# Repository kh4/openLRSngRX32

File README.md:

openLRSngRX32
=============

OpenLRS compatible 12 channel RX based on STM32F103. Can use up to 2 RFM22B radio modules for true diversity and supports additional MPU6050 for integrated flightcontrol.

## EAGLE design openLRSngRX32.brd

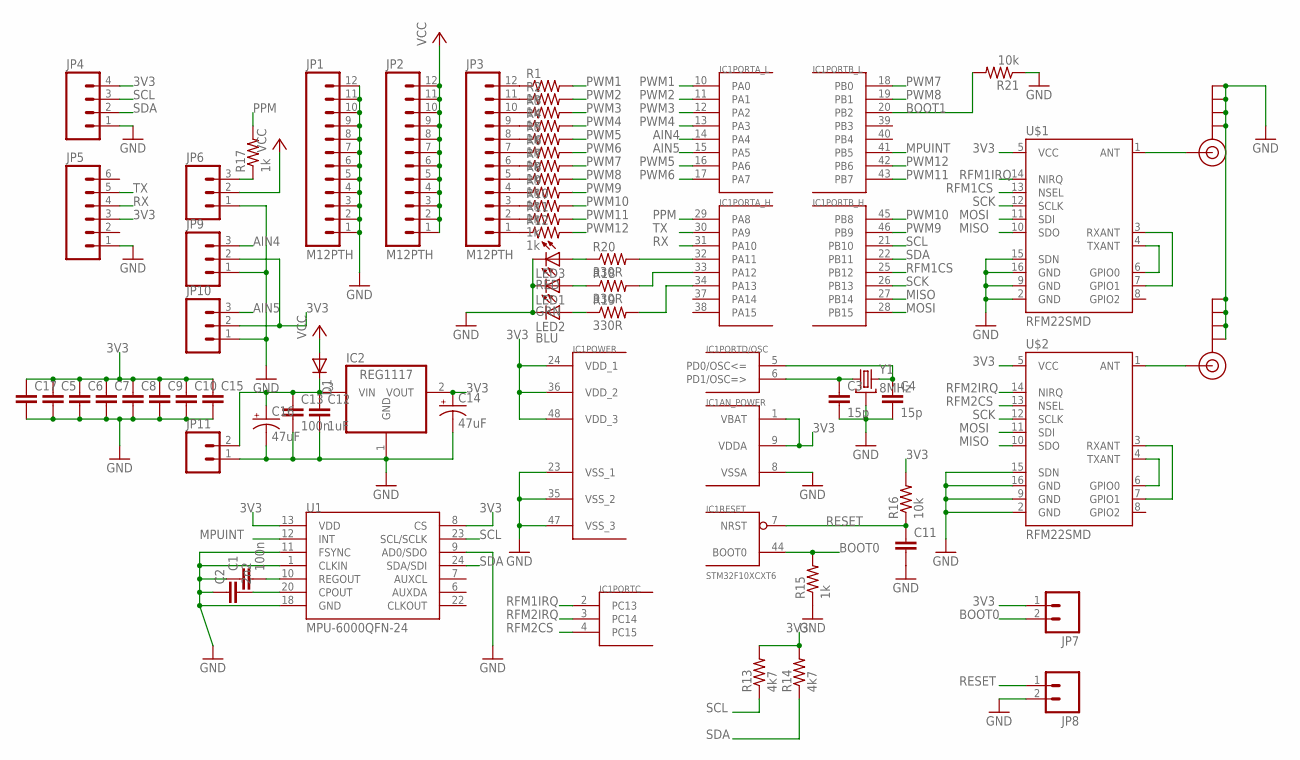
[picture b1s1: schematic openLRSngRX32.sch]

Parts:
C1, C13: 100n; 0805
C2: 2n2; 0805
C3, C4: 15p; 0805
C5, C6, C7, C8, C9, C10, C11, C15, C17: CAP0805; 0805
C12: 1uF; 0805
C14, C16: 47uF; EIA3528
D1: DIODE-DO-214AC; DO-214AC
IC1: STM32F10XCXT6; TQFP48
IC2: REG1117; SOT223
J$1, J$2: SMA_EDGE; SMA-EDGE
JP1, JP2, JP3: M12PTH; 1X12
JP4: M04PTH; 1X04
JP5: M06SIP; 1X06
JP6, JP9, JP10: M03PTH; 1X03
JP7, JP8, JP11: M02PTH; 1X02
LED1: GRN; SML0805
LED2: BLU; SML0805
LED3: RED; SML0805
R1, R2, R3, R4, R5, R6, R7, R8, R9, R10, R11, R12, R15, R17: 1k; 0805
R13, R14: 4k7; 0805
R16, R21: 10k; 0805
R18, R19, R20: 330R; 0805
U1: MPU-6000QFN-24; QFN-24-TESTING
U$1, U$2: RFM22SMD; RFM22-XXX-S2
Y1: 8MHz; CRYSTAL-SMD-5X3

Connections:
3V3: C5.1, C6.1, C7.1, C8.1, C9.1, C10.1, C14.A (+), C15.1, C17.1, IC1.1 (VBAT), IC1.9 (VDDA), IC1.24 (VDD_1), IC1.36 (VDD_2), IC1.48 (VDD_3), IC2.2 (VOUT), JP4.4, JP5.3, JP7.1, JP9.2, JP10.2, R13.2, R14.2, R16.2, U1.8 (CS), U1.13 (VDD), U$1.5 (VCC), U$2.5 (VCC)
AIN4: IC1.14 (PA4), JP9.3
AIN5: IC1.15 (PA5), JP10.3
BOOT0: IC1.44 (BOOT0), JP7.2, R15.2
BOOT1: IC1.20 (PB2), R21.2
GND: C1.1, C2.1, C3.2, C4.2, C5.2, C6.2, C7.2, C8.2, C9.2, C10.2, C11.2, C12.2, C13.2, C14.C (-), C15.2, C16.C (-), C17.2, IC1.8 (VSSA), IC1.23 (VSS_1), IC1.35 (VSS_2), IC1.47 (VSS_3), IC2.1 (GND), J$1.GND@0 (GND), J$1.GND@1 (GND), J$1.GND@2 (GND), J$1.GND@3 (GND), J$2.GND@0 (GND), J$2.GND@1 (GND), J$2.GND@2 (GND), J$2.GND@3 (GND), JP1.1, JP1.2, JP1.3, JP1.4, JP1.5, JP1.6, JP1.7, JP1.8, JP1.9, JP1.10, JP1.11, JP1.12, JP4.1, JP5.1, JP6.1, JP8.2, JP9.1, JP10.1, JP11.1, LED1.C, LED2.C, LED3.C, R15.1, R21.1, U1.1 (CLKIN), U1.9 (AD0/SDO), U1.11 (FSYNC), U1.18 (GND), U$1.2 (GND), U$1.9 (GND), U$1.15 (SDN), U$1.16 (GND), U$2.2 (GND), U$2.9 (GND), U$2.15 (SDN), U$2.16 (GND), Y1.2 (GND), Y1.4 (GND)
MISO: IC1.27 (PB14), U$1.10 (SDO), U$2.10 (SDO)
MOSI: IC1.28 (PB15), U$1.11 (SDI), U$2.11 (SDI)
MPUINT: IC1.41 (PB5), U1.12 (INT)
unnamed: JP3.12, R1.1
unnamed: JP3.11, R2.1
unnamed: JP3.10, R3.1
unnamed: JP3.9, R4.1
unnamed: JP3.8, R5.1
unnamed: JP3.7, R6.1
unnamed: JP3.6, R7.1
unnamed: JP3.5, R8.1
unnamed: JP3.4, R9.1
unnamed: JP3.3, R10.1
unnamed: JP3.2, R11.1
unnamed: JP3.1, R12.1
unnamed: J$2.SIG (SIGNAL), U$2.1 (ANT)
unnamed: C1.2, U1.10 (REGOUT)
unnamed: C2.2, U1.20 (CPOUT)
unnamed: C4.1, IC1.5 (PD0/OSC<=), Y1.3 (2)
unnamed: C3.1, IC1.6 (PD1/OSC=>), Y1.1
unnamed: J$1.SIG (SIGNAL), U$1.1 (ANT)
unnamed: U$2.4 (TXANT), U$2.6 (GPIO0)
unnamed: U$2.3 (RXANT), U$2.7 (GPIO1)
unnamed: U$1.4 (TXANT), U$1.6 (GPIO0)
unnamed: U$1.3 (RXANT), U$1.7 (GPIO1)
unnamed: JP6.3, R17.1
unnamed: C12.1, C13.1, C16.A (+), D1.C, IC2.3 (VIN), JP11.2
unnamed: LED3.A, R20.1
unnamed: LED1.A, R18.1
unnamed: LED2.A, R19.1
unnamed: IC1.32 (PA11), R20.2
unnamed: IC1.33 (PA12), R18.2
unnamed: IC1.34 (PA13), R19.2
PPM: IC1.29 (PA8), R17.2
PWM1: IC1.10 (PA0), R1.2
PWM2: IC1.11 (PA1), R2.2
PWM3: IC1.12 (PA2), R3.2
PWM4: IC1.13 (PA3), R4.2
PWM5: IC1.16 (PA6), R5.2
PWM6: IC1.17 (PA7), R6.2
PWM7: IC1.18 (PB0), R7.2
PWM8: IC1.19 (PB1), R8.2
PWM9: IC1.46 (PB9), R9.2
PWM10: IC1.45 (PB8), R10.2
PWM11: IC1.43 (PB7), R11.2
PWM12: IC1.42 (PB6), R12.2
RESET: C11.1, IC1.7 (NRST), JP8.1, R16.1
RFM1CS: IC1.25 (PB12), U$1.13 (NSEL)
RFM1IRQ: IC1.2 (PC13), U$1.14 (NIRQ)
RFM2CS: IC1.4 (PC15), U$2.13 (NSEL)
RFM2IRQ: IC1.3 (PC14), U$2.14 (NIRQ)
RX: IC1.31 (PA10), JP5.4
SCK: IC1.26 (PB13), U$1.12 (SCLK), U$2.12 (SCLK)
SCL: IC1.21 (PB10), JP4.3, R13.1, U1.23 (SCL/SCLK)
SDA: IC1.22 (PB11), JP4.2, R14.1, U1.24 (SDA/SDI)
TX: IC1.30 (PA9), JP5.5
VCC: D1.A, JP2.1, JP2.2, JP2.3, JP2.4, JP2.5, JP2.6, JP2.7, JP2.8, JP2.9, JP2.10, JP2.11, JP2.12, JP6.2

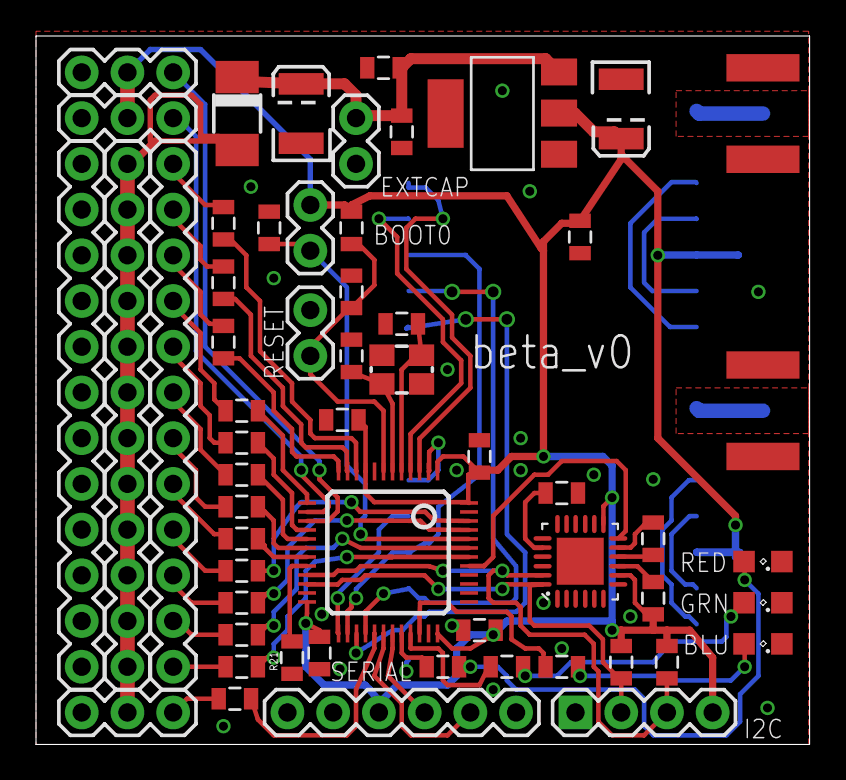
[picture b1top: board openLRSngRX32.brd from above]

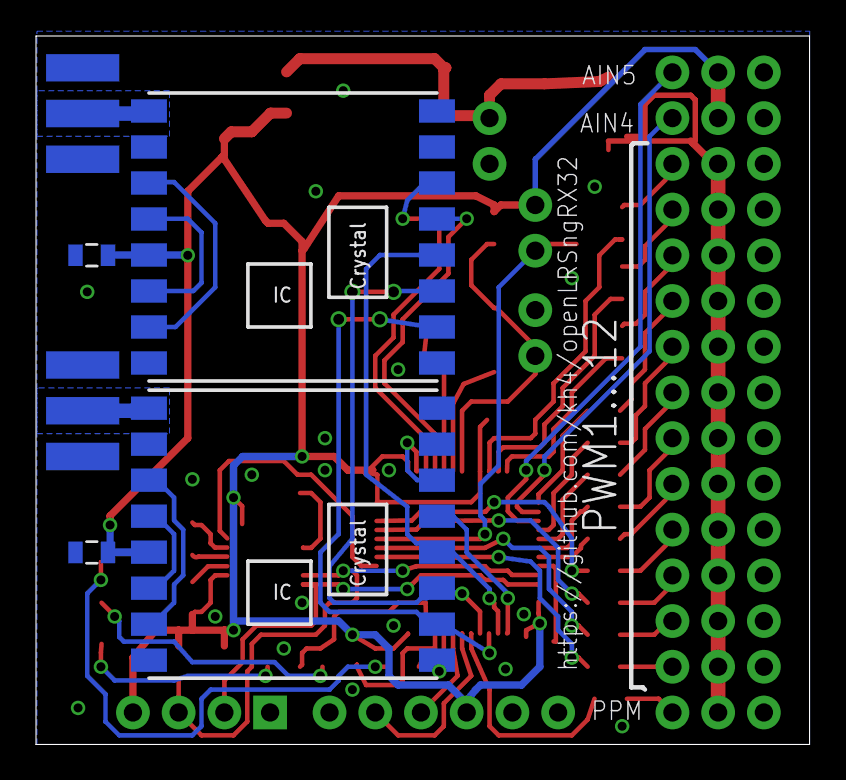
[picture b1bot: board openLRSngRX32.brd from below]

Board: 2 copper layers, 43.0 x 39.4 mm, 61 parts (6 on the bottom side), 63 nets.

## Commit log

2013-04-04 initial
2013-04-04 removing project file (not needed)
2013-04-04 - remove project - working onwards...
2013-04-04 hope the project is gone now ... (damn tortoise git)
2013-04-04 some more caps
2013-04-04 board
2013-04-05 Add .gitignore Board routing
2013-04-05 ...almost done
2013-04-05 more cs lines
2013-04-05 MPU interrupt GND reinforcement
2013-04-05 minor board tuning
2013-04-06 Last fixes... I hope
2013-04-06 cleanup
2013-04-08 tuning still
2013-04-08 GB leds
2013-04-08 some silk
2013-04-08 silk
2013-04-08 beta_v0
2013-04-27 Fix missing BOOT1 pulldown.
2013-04-27 missed some airwires on last commit...
2013-05-28 Add license

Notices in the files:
parts and their libraries:
SparkFun-RF: Licensing: CC v3.0 Share-Alike You are welcome to use this library for commercial purposes.
